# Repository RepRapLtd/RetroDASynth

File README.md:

# RetroDASynth

**RetroDASynth** is an open-source project to build a modular, polyphonic, retro-style electronic music synthesiser from inexpensive, readily available components. Its central idea is to use **the same general-purpose circuit board for different synthesiser modules**: load different software onto its microcontroller, and the board can become a voltage-controlled oscillator (VCO), a voltage-controlled filter (VCF), an envelope generator, or potentially another audio or control function. Modules can then be connected to make different instruments and signal-processing arrangements.

The design aims to be accessible to hobbyists: through-hole components where practicable, hand-solderable PCBs, 3D-printable mechanical parts, straightforward 5 V power, and published hardware and software. The ultimate aim is a self-contained, MIDI-controlled, polyphonic instrument, with sequencing and facilities for experimenting with the signal chain.

It is being created by Adrian Bowyer with significant inputs from ChatGPT.

## The prototype so far

The photograph above shows the current experimental system. **A working monophonic MIDI-controlled voice** has been demonstrated, using:

- An **Arduino UNO R4 WiFi** as the MIDI receiver and controller. It reads MIDI note messages, generates a pitch-control voltage and drives an active-low gate output.
- An **AVR32DA28** programmed as a VCO, producing audio using its internal DAC.
- A second **AVR32DA28** programmed as an envelope generator; its control voltage adjusts the VCO's output level.
- An **MCP6004** quad operational amplifier for analogue buffering and related signal conditioning.
- A **128 × 64 I²C OLED** on the Arduino, showing MIDI status, the last note, velocity and current monophonic voice activity.

The complete assembled prototype runs from a **single regulated 5 V supply**. In one test it drew approximately **109 mA** at 5 V (about 0.55 W), and played in tune. That measurement is for the present prototype, not a forecast for the finished polyphonic instrument.

## One board, several functions

The common module design is based on the **Microchip AVR32DA28**, a 28-pin, through-hole microcontroller with analogue-to-digital conversion, a digital-to-analogue converter, timers and digital I/O. The idea is to standardise the connections to controls, patch sockets and power, while changing the firmware to determine each module's behaviour.

The following functions have been developed and tested experimentally:

### Voltage-controlled oscillator (VCO)

- Produces **sine**, **triangle/sawtooth**, **square/pulse**, and **noise** waveforms.
- Waveform selection, pitch, shape and amplitude are voltage- or switch-controlled.
- Uses the AVR's **10-bit DAC**, driven by a timer-based waveform generator.
- Provides a low-frequency mode, allowing the same oscillator design to generate slowly varying control signals.
- Uses a pitch relationship of approximately **0.75 V per octave** in the present software; this is a project-specific convention, **not** the more usual 1 V/octave analogue-synthesiser standard.
- The analogue circuit provides buffered and inverted outputs. A filtered PWM signal establishes the reference needed for the complementary output.

### Voltage-controlled filter (VCF)

- A software-defined, two-pole **state-variable filter**, developed and tested on the AVR32DA28.
- Switch-selectable **low-pass, high-pass, band-pass and notch** responses.
- Voltage-controlled cutoff and resonance, with an option to experiment with self-oscillation.
- Processes an analogue audio input through the microcontroller's ADC and DAC.

This filter has been tested as a separate module; it is **not yet part of the MIDI-controlled voice shown in the prototype photograph**. Input bias handling and gain/headroom are subjects for further development.

### Envelope generator

- Produces a control voltage in response to a gate signal.
- Adjustable attack, decay and level, with several selectable envelope shapes.
- Supports experiments with gated and one-shot behaviour.
- In the present prototype, the envelope controls the VCO's output amplitude.

## MIDI controller and display

The Arduino UNO R4 WiFi currently receives **DIN MIDI** via a MIDI shield and operates in a simple **monophonic** mode. Its DAC output on **A0** supplies pitch CV; digital pin **D2** supplies the active-low envelope gate. The small OLED is connected over I²C.

The current display shows the last MIDI note, its velocity, whether the single voice is active, and basic MIDI status. Features such as channel selection, polyphonic voice allocation, sustain-pedal handling and sequencing are **planned, not yet implemented**.

The prototype currently uses the R4's built-in DAC for pitch. For the polyphonic design, the intention is to use **a separate dual-channel, 12-bit SPI DAC for each voice** (a possible device is the through-hole **MCP4822**), providing independent **pitch and velocity/control voltages**. This is a design proposal, not an installed part of the photographed prototype.

## Intended polyphonic architecture

The proposed arrangement is:

1. The central Arduino receives MIDI and, eventually, runs a sequencer and allocates notes to available voices.
2. Each voice has its own pitch and amplitude-control voltages, plus an envelope gate.
3. Each voice is assembled from common programmable modules, initially an oscillator and envelope generator, with filters added as desired.
4. The audio outputs are mixed to produce the instrument's final sound.

A first polyphonic build will probably have a modest number of voices, with the design able to expand. Voice stealing, MIDI sustain and channel-specific controls will be addressed as the instrument develops.

## Hardware and software

The repository is organised into:

- [`Electronics/`](Electronics/) — electronic design material.
- [`Software/`](Software/) — firmware and related software.
- [`Docs/`](Docs/) — documentation.
- [`Pix/`](Pix/) — photographs and illustrations, including the prototype picture above.

Firmware development uses the **Arduino IDE** and **DxCore** for the AVR DA-series microcontrollers. The MIDI controller uses the Arduino UNO R4 WiFi environment. The electronic design work uses **KiCad**.

**Project status:** experimental development. The circuits and programs are evolving, and a tested breadboard prototype should not be mistaken for a final, documented, ready-to-build kit.

## Next steps

- Develop and manufacture the standard through-hole module PCB.
- Extend the controller from one note to multiple independently allocated voices.
- Move pitch and velocity/control outputs to external, per-voice SPI DACs.
- Add MIDI channel selection, diagnostics and sustain-pedal support.
- Integrate the filter into complete voices, and develop audio mixing.
- Add sequencing, and develop the interlocking 3D-printed module/panel system.

## Licence

This repository includes the [GNU General Public License, version 3](LICENSE). See that file for the applicable licence terms.

## Written by

Adrian Bowyer and ChatGPT

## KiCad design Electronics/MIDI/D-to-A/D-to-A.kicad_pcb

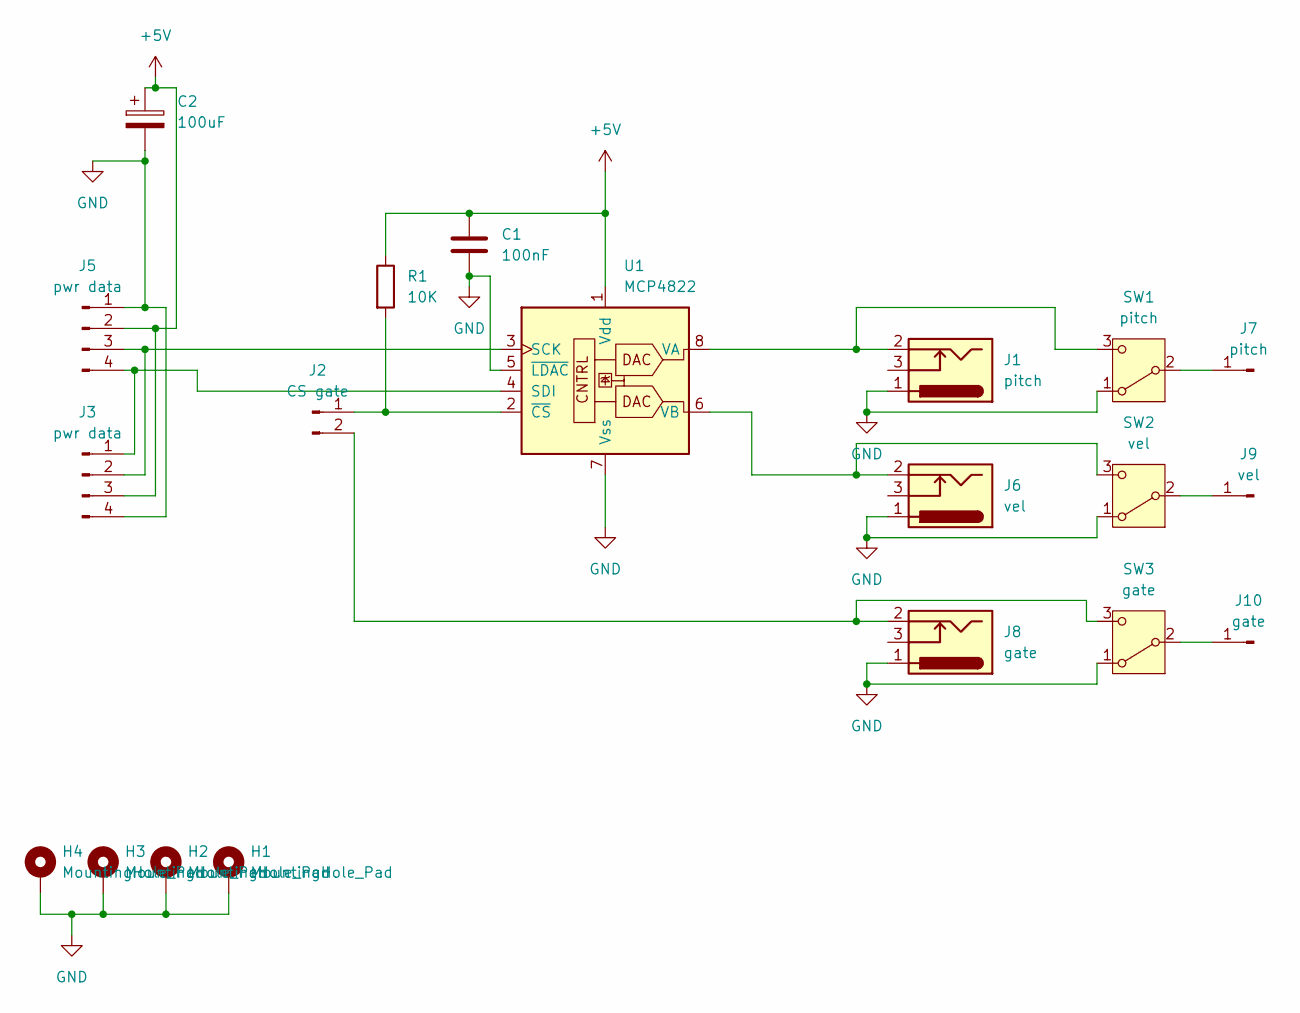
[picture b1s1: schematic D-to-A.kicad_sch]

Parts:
C1: 100nF; C_Disc_D3.4mm_W2.1mm_P2.50mm
C2: 100uF; CP_Radial_D6.3mm_P2.50mm
H1, H2, H3, H4: MountingHole_Pad; MountingHole_3.2mm_M3_DIN965_Pad
J1: pitch; barrel_jack_switch
J2: CS gate; PinHeader_1x02_P2.54mm_Horizontal
J3, J5: pwr data; PinHeader_1x04_P2.54mm_Horizontal
J6: vel; barrel_jack_switch
J7: pitch; PinHeader_1x01_P2.54mm_Horizontal
J8: gate; barrel_jack_switch
J9: vel; PinHeader_1x01_P2.54mm_Horizontal
J10: gate; PinHeader_1x01_P2.54mm_Horizontal
R1: 10K; R_Axial_DIN0204_L3.6mm_D1.6mm_P5.08mm_Horizontal
SW1: pitch; SW_1P2W
SW2: vel; SW_1P2W
SW3: gate; SW_1P2W
U1: MCP4822; DIP-8_W7.62mm

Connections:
+5V: C1.1, C2.1, J3.3, J5.2, R1.1, U1.1 (Vdd)
GND: C1.2, C2.2, H1.1 (1_1), H2.1 (1_1), H3.1 (1_1), H4.1 (1_1), J1.1, J3.4, J5.1, J6.1, J8.1, SW1.1 (A), SW2.1 (A), SW3.1 (A), U1.5 (~LDAC), U1.7 (Vss)
unnamed: J2.1, R1.2, U1.2 (~CS)
unnamed: J2.2, J8.2, SW3.3 (C)
unnamed: J3.1, J5.4, U1.4 (SDI)
unnamed: J3.2, J5.3, U1.3 (SCK)
unnamed: J7.1 (Pin_1_1), SW1.2 (B)
unnamed: J9.1 (Pin_1_1), SW2.2 (B)
unnamed: J10.1 (Pin_1_1), SW3.2 (B)
unnamed: J1.2, SW1.3 (C), U1.8 (VA)
unnamed: J6.2, SW2.3 (C), U1.6 (VB)

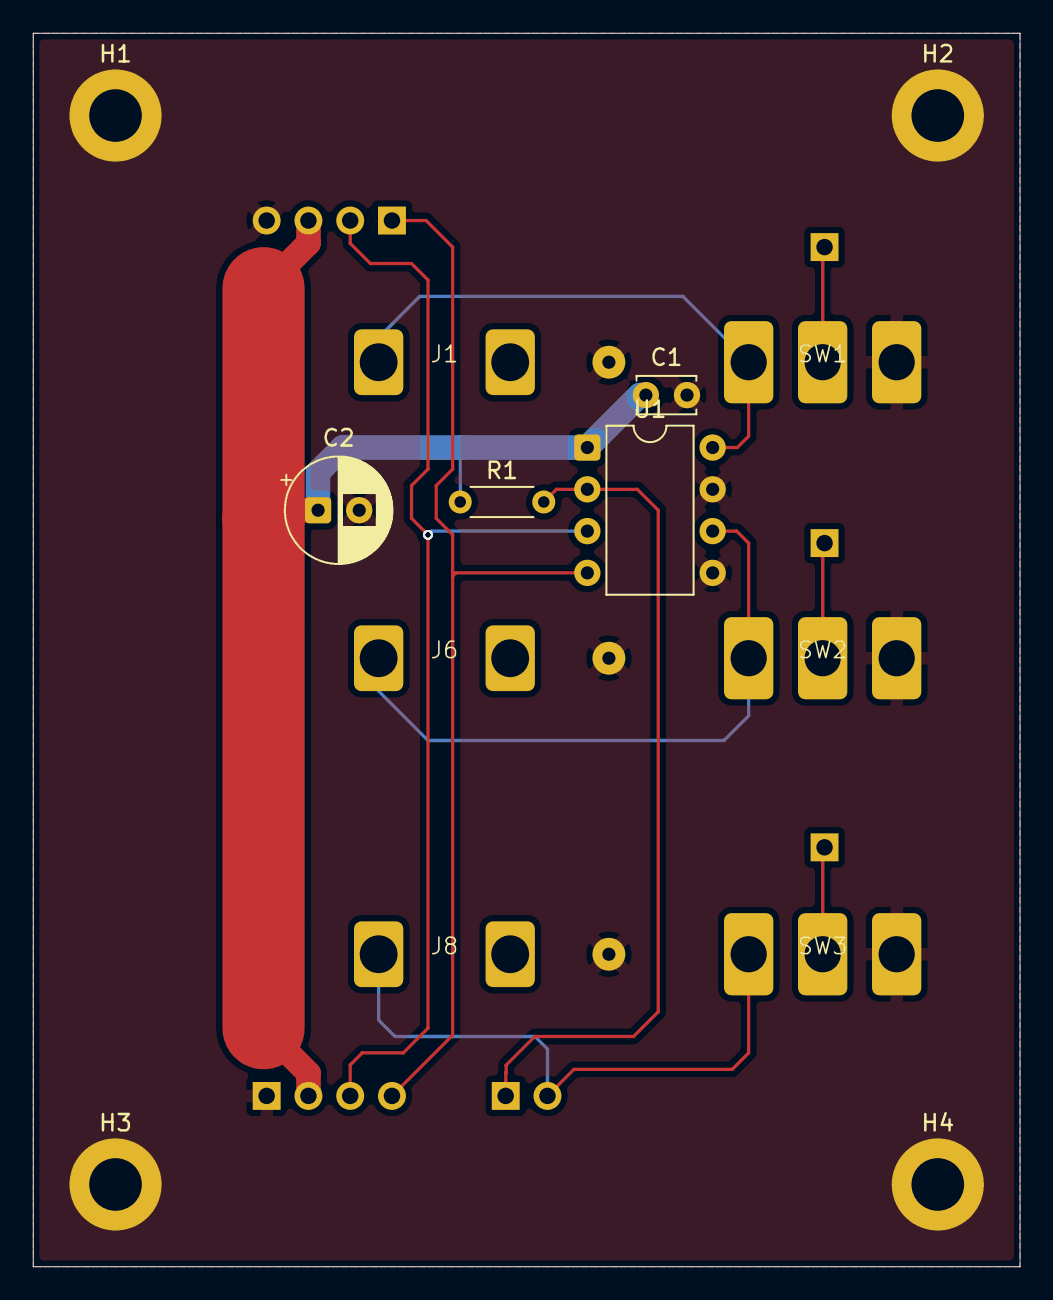
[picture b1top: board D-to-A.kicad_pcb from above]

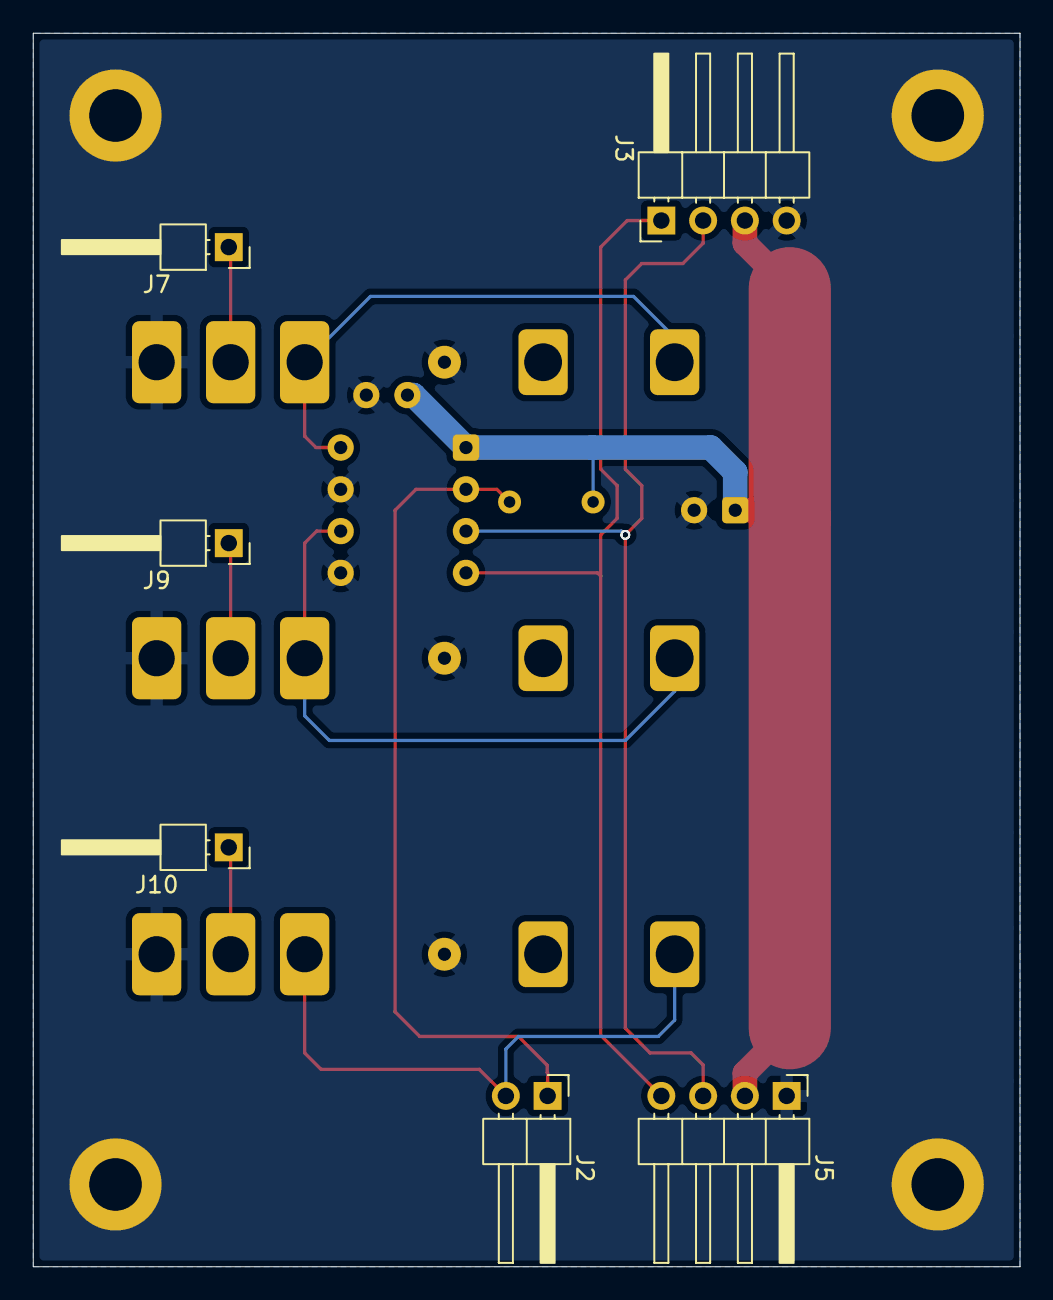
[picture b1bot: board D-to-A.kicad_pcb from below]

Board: 2 copper layers, 60.0 x 75.0 mm, 20 parts (6 on the bottom side), 11 nets.

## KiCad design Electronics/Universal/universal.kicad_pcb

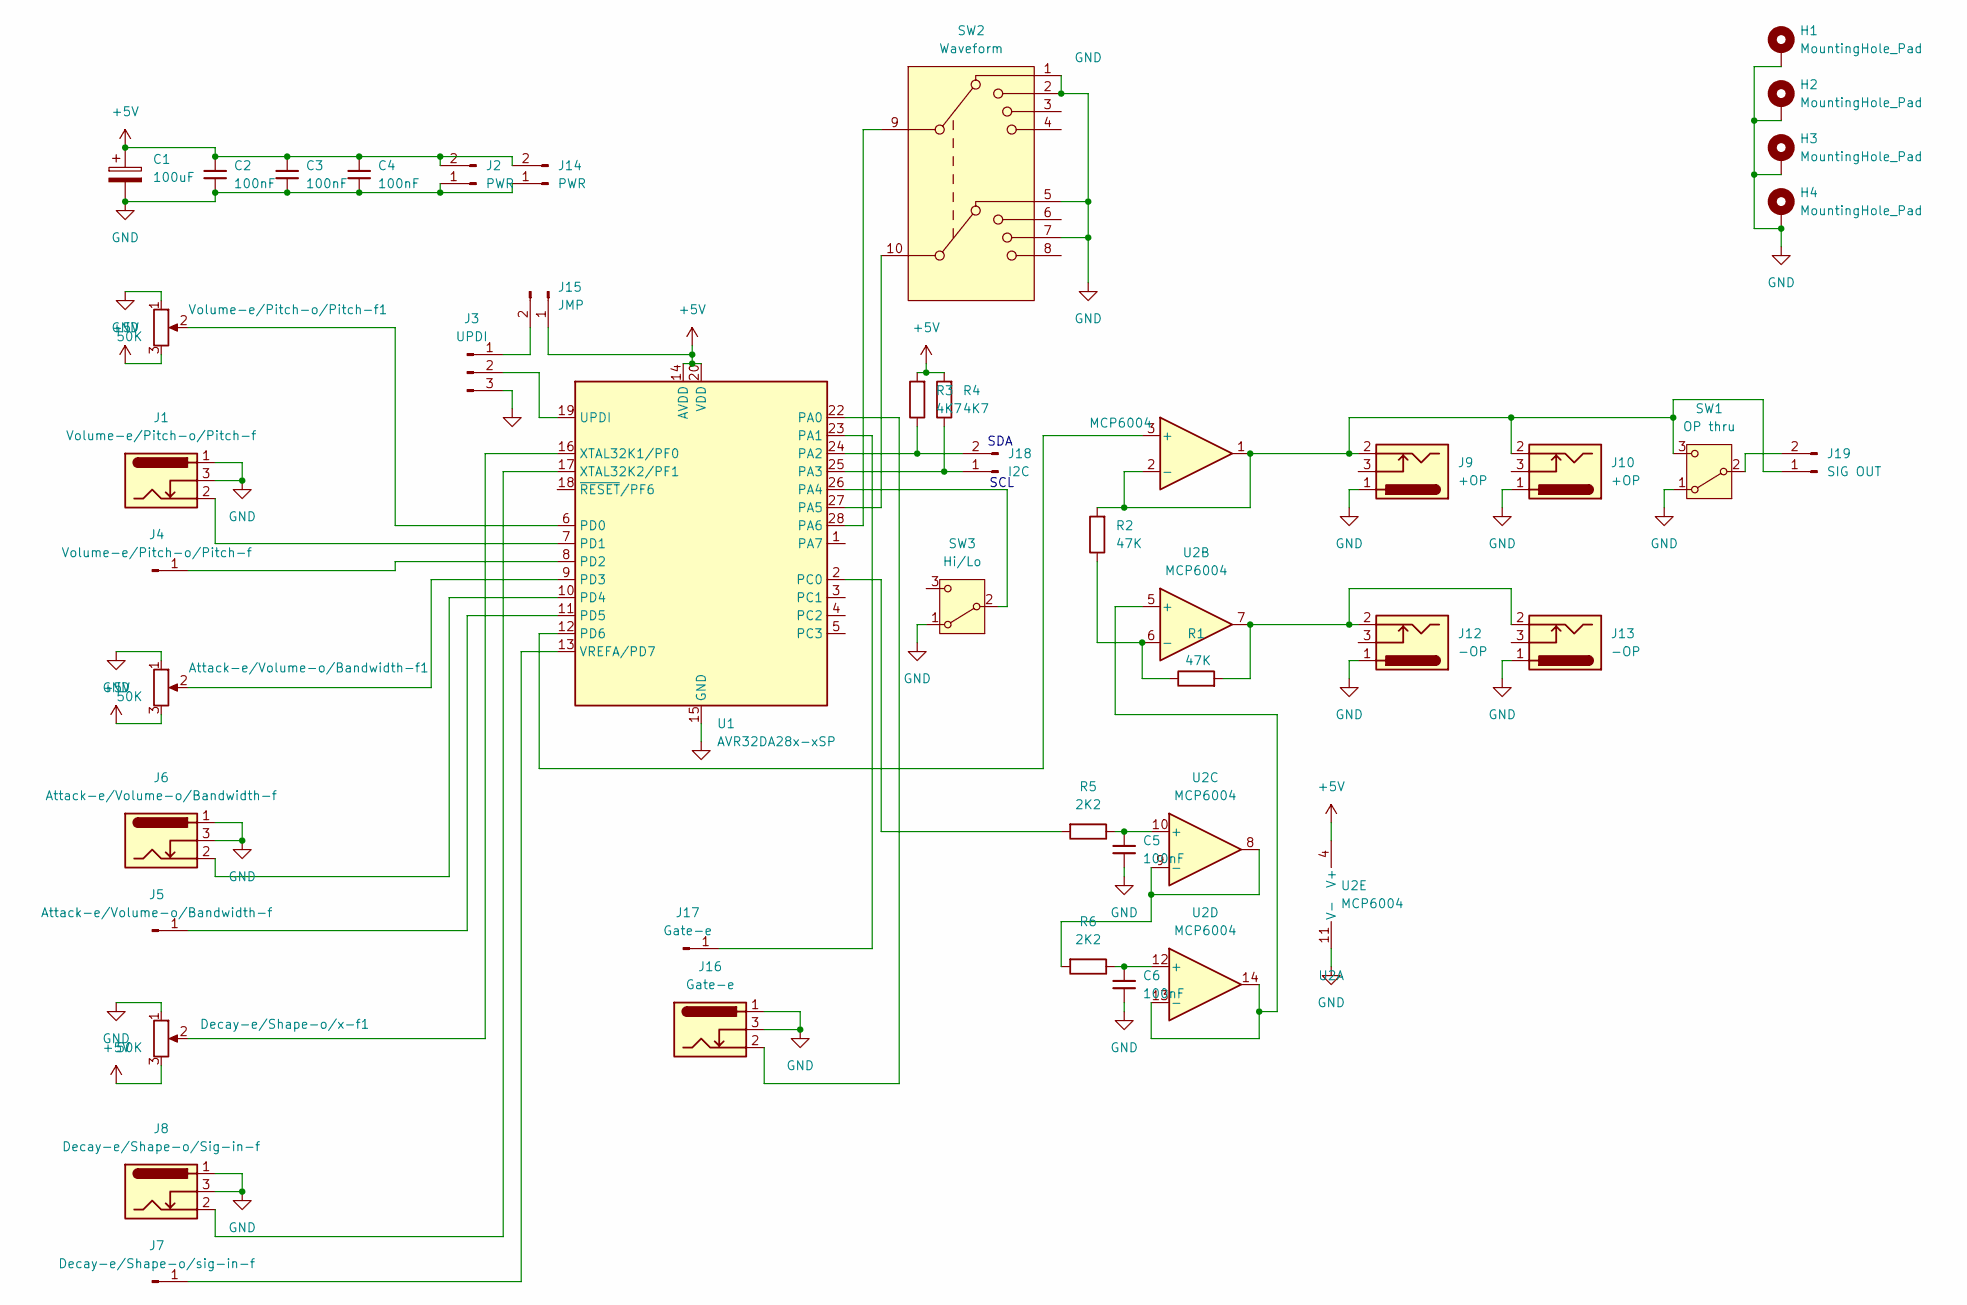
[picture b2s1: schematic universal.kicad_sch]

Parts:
Attack-e/Volume-o/Bandwidth-f1: 50K; Potentiometer_Alpha_RD901F-40-00D_Single_Vertical
C1: 100uF; C_Radial_D6.3mm_H11.0mm_P2.50mm
C2, C3, C4, C5, C6: 100nF; C_Disc_D3.0mm_W1.6mm_P2.50mm
Decay-e/Shape-o/x-f1: 50K; Potentiometer_Alpha_RD901F-40-00D_Single_Vertical
H1, H2, H3, H4: MountingHole_Pad; MountingHole_3.2mm_M3_Pad
J1: Volume-e/Pitch-o/Pitch-f; barrel_jack_switch
J2, J14: PWR; PinHeader_1x02_P2.54mm_Horizontal
J3: UPDI; PinSocket_1x03_P2.54mm_Vertical
J4: Volume-e/Pitch-o/Pitch-f; PinHeader_1x01_P2.54mm_Horizontal
J5: Attack-e/Volume-o/Bandwidth-f; PinHeader_1x01_P2.54mm_Horizontal
J6: Attack-e/Volume-o/Bandwidth-f; barrel_jack_switch
J7: Decay-e/Shape-o/sig-in-f; PinHeader_1x01_P2.54mm_Horizontal
J8: Decay-e/Shape-o/Sig-in-f; barrel_jack_switch
J9, J10: +OP; barrel_jack_switch
J12, J13: -OP; barrel_jack_switch
J15: JMP; PinHeader_1x02_P2.54mm_Vertical
J16: Gate-e; barrel_jack_switch
J17: Gate-e; PinHeader_1x01_P2.54mm_Horizontal
J18: I2C; PinHeader_1x02_P2.54mm_Vertical
J19: SIG OUT; PinHeader_1x02_P2.54mm_Horizontal
R1, R2: 47K; R_Axial_DIN0204_L3.6mm_D1.6mm_P5.08mm_Horizontal
R3, R4: 4K7; R_Axial_DIN0204_L3.6mm_D1.6mm_P5.08mm_Horizontal
R5, R6: 2K2; R_Axial_DIN0204_L3.6mm_D1.6mm_P5.08mm_Horizontal
SW1: OP thru; SW_1P2W
SW2: Waveform; rotary_2p4w
SW3: Hi/Lo; SW_1P2W
U1: AVR32DA28x-xSP; DIP-28_W7.62mm
U2: MCP6004; DIP-14_W7.62mm
Volume-e/Pitch-o/Pitch-f1: 50K; Potentiometer_Alpha_RD901F-40-00D_Single_Vertical

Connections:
+5V: Attack-e/Volume-o/Bandwidth-f1.3, C1.1, C2.1, C3.1, C4.1, Decay-e/Shape-o/x-f1.3, J2.2, J14.2, J15.1, R3.2, R4.2, U1.14 (AVDD), U1.20 (VDD), U2.4 (V+), Volume-e/Pitch-o/Pitch-f1.3
GND: Attack-e/Volume-o/Bandwidth-f1.1, C1.2, C2.2, C3.2, C4.2, C5.2, C6.2, Decay-e/Shape-o/x-f1.1, H1.1 (1_1), H2.1 (1_1), H3.1 (1_1), H4.1 (1_1), J1.1, J1.3, J2.1, J3.3, J6.1, J6.3, J8.1, J8.3, J9.1, J10.1, J12.1, J13.1, J14.1, J16.1, J16.3, SW1.1 (A), SW2.1, SW2.2, SW2.5, SW2.7, SW3.1 (A), U1.15 (GND), U1.21 (GND), U2.11 (V-), Volume-e/Pitch-o/Pitch-f1.1
unnamed: J3.2, U1.19 (UPDI)
unnamed: J4.1 (Pin_1_1), U1.8 (PD2)
unnamed: J5.1 (Pin_1_1), U1.11 (PD5)
unnamed: J7.1 (Pin_1_1), U1.13 (VREFA/PD7)
unnamed: J12.2, J13.2, R1.2, U2.7
unnamed: J3.1, J15.2
unnamed: J17.1 (Pin_1_1), U1.23 (PA1)
unnamed: J18.1, R4.1, U1.25 (PA3)
unnamed: J18.2, R3.1, U1.24 (PA2)
unnamed: J9.2, J10.2, J19.1, R2.2, SW1.3 (C), U2.1, U2.2 (-)
unnamed: J19.2, SW1.2 (B)
unnamed: SW3.2 (B), U1.26 (PA4)
unnamed: J16.2, U1.22 (PA0)
unnamed: SW2.10, U1.27 (PA5)
unnamed: SW2.9, U1.28 (PA6)
unnamed: R5.2, U1.2 (PC0)
unnamed: U1.6 (PD0), Volume-e/Pitch-o/Pitch-f1.2
unnamed: J1.2, U1.7 (PD1)
unnamed: Attack-e/Volume-o/Bandwidth-f1.2, U1.9 (PD3)
unnamed: J6.2, U1.10 (PD4)
unnamed: U1.12 (PD6), U2.3 (+)
unnamed: Decay-e/Shape-o/x-f1.2, U1.16 (XTAL32K1/PF0)
unnamed: J8.2, U1.17 (XTAL32K2/PF1)
unnamed: U2.5 (+), U2.13 (-), U2.14
unnamed: R1.1, R2.1, U2.6 (-)
unnamed: C5.1, R5.1, U2.10 (+)
unnamed: R6.2, U2.8, U2.9 (-)
unnamed: C6.1, R6.1, U2.12 (+)

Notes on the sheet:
SCL
SDA

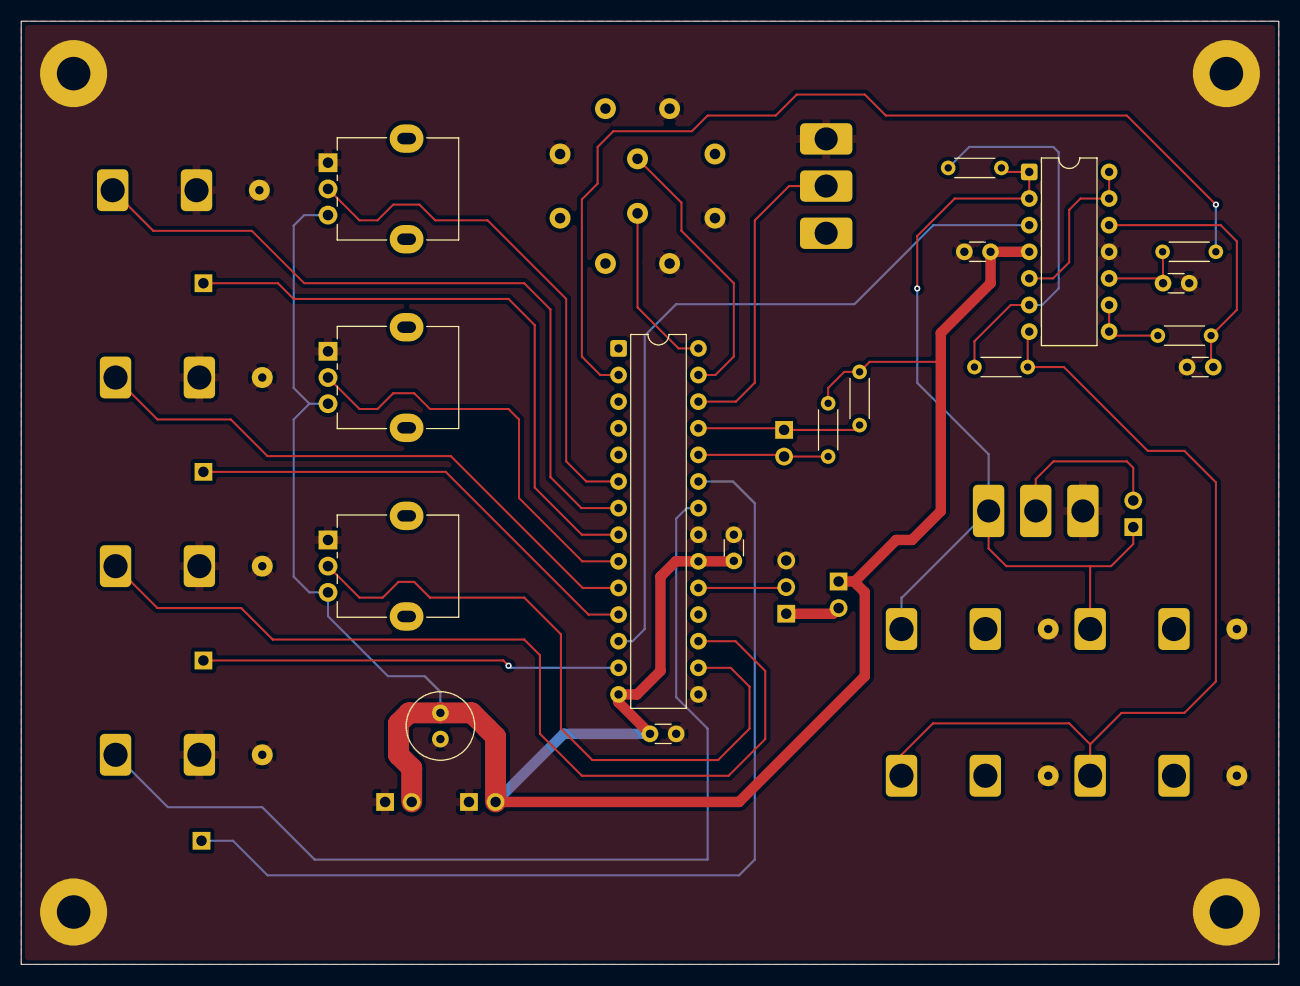
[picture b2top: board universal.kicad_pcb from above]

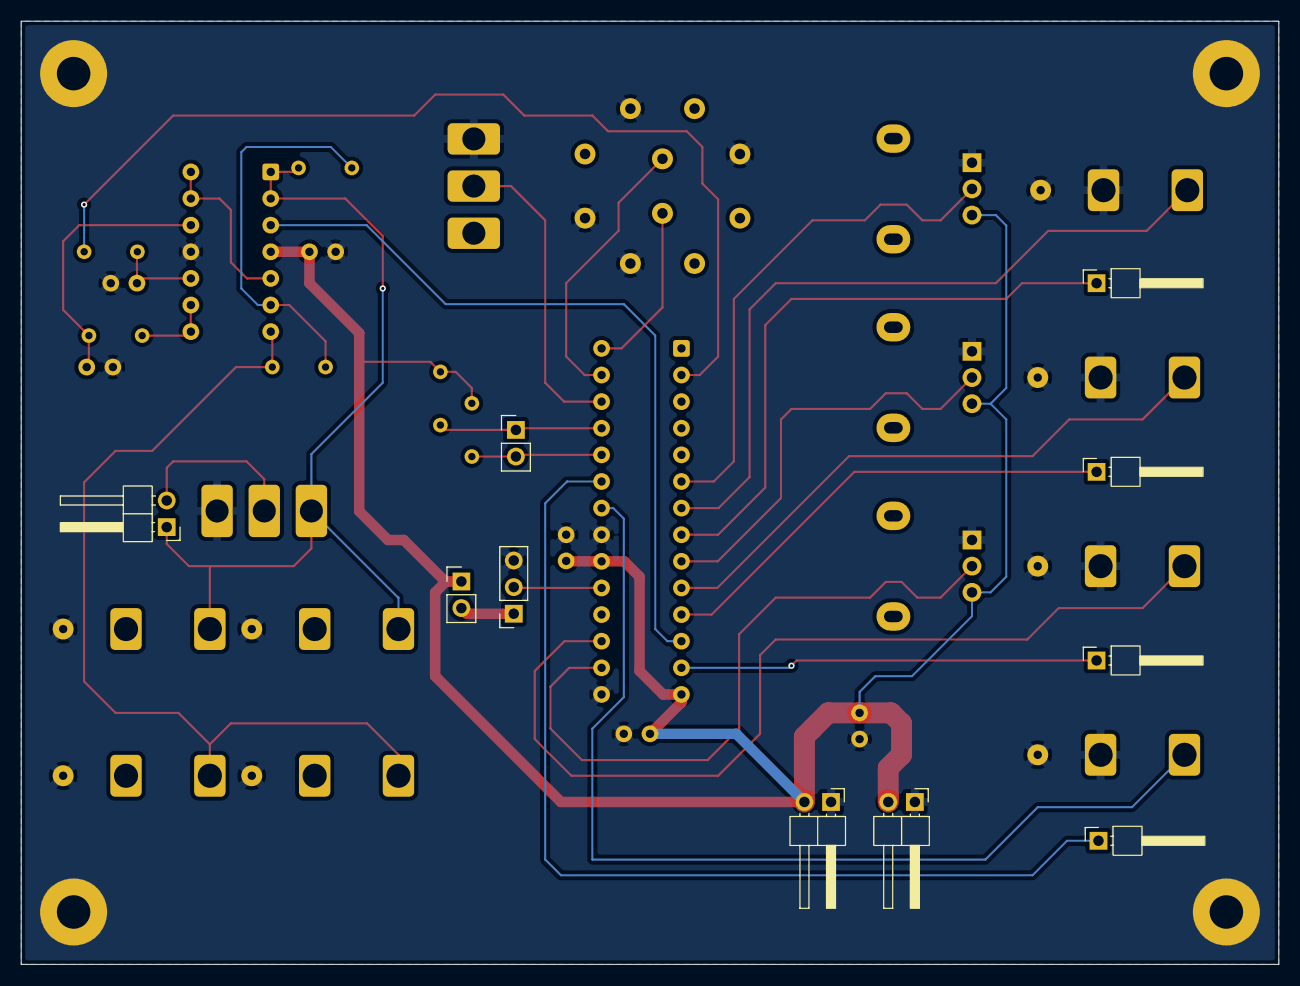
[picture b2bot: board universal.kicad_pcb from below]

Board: 2 copper layers, 120.0 x 90.0 mm, 42 parts (10 on the bottom side), 30 nets.

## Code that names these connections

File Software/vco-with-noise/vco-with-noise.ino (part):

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//
// DxCore 1.6.2, 24 MHz internal clock
//
// PD0  Pitch CV
// PD1  Pitch CV
// PD2  Pitch CV
// PD3  Volume CV
// PD4  Volume CV
// PD5  Volume CV
// PD7  Shape CV
// PF0  Shape CV
// PF1  Shape CV
// PD6  10-bit DAC output
//
// PC0  PWM reference output (93.75 kHz)
//
// PA4  Frequency range (LOW = low range)
// PA5  Waveform bit 0
// PA6  Waveform bit 1
//
// Waveforms:
//   3 Sine
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// TCA0, single-slope PWM
// 24 MHz / 256 = 93750 Hz
//
// WO0 routed to PC0.
// ============================================================

void setupPWM()
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  PORTMUX.TCAROUTEA =
      PORTMUX_TCA0_PORTC_gc;

  pinMode(PIN_PC0, OUTPUT);

  TCA0.SINGLE.CTRLA = 0;

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
void setup()
{
  pinMode(PIN_PA4, INPUT_PULLUP);
  pinMode(PIN_PA5, INPUT_PULLUP);
  pinMode(PIN_PA6, INPUT_PULLUP);

  pinMode(PIN_PD0, INPUT);
  pinMode(PIN_PD1, INPUT);
  pinMode(PIN_PD2, INPUT);
  pinMode(PIN_PD3, INPUT);
  pinMode(PIN_PD4, INPUT);
  pinMode(PIN_PD5, INPUT);
  pinMode(PIN_PD7, INPUT);
  pinMode(PIN_PF0, INPUT);
  pinMode(PIN_PF1, INPUT);
    
  analogReadResolution(12);
  analogReference(VDD);
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      (VREF.ADC0REF & ~VREF_REFSEL_gm) |
      VREF_REFSEL_VDD_gc;

  (void)analogRead(PIN_PD0);
  (void)analogRead(PIN_PD1);
  (void)analogRead(PIN_PD2);
  (void)analogRead(PIN_PD3);
  (void)analogRead(PIN_PD4);
  (void)analogRead(PIN_PD5);
  (void)analogRead(PIN_PD7);
  (void)analogRead(PIN_PF0);
  (void)analogRead(PIN_PF1);

  // Enable DAC
  DACReference(VDD);
  analogWrite(PIN_PD6, 128);
  DAC0.DATA = 0;

  // PWM reference output
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
  // ---- Read analogue controls ----

  uint16_t pitchADC = analogRead(PIN_PD0)
                  + analogRead(PIN_PD1)
                  + analogRead(PIN_PD2);

  uint16_t volumeADC =
      analogRead(PIN_PD3)
      + analogRead(PIN_PD4)
      + analogRead(PIN_PD5);
      
  uint16_t shapeADC = analogRead(PIN_PD7)
      + analogRead(PIN_PF0)
      + analogRead(PIN_PF1);

  // ---- Waveform selection ----

  uint8_t selected =
      (!digitalRead(PIN_PA5) ? 0 : 1) |
      (!digitalRead(PIN_PA6) ? 0 : 2);

  uint8_t shape = shapeADC >> 4;

  bool lowRange = !digitalRead(PIN_PA4);
  bool drifting = (selected == 3 && lowRange);

  if (selected != oldWaveform ||
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
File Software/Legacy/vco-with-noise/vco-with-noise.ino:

#include <Arduino.h>
#include <math.h>

// -------- User settings --------

const uint8_t DAC_P   = PIN_PA6;
const uint8_t CV_P    = PIN_PA2;
const uint8_t WAVE_P  = PIN_PA1;
const uint8_t SHAPE_P = PIN_PA3;
const uint8_t AMP_P   = PIN_PA7;  // NEW

const uint32_t SAMPLE_RATE = 40000;

const float MIN_FREQ = 50.0f;
const float VOLTS_PER_OCTAVE = 0.75f;
const float SUPPLY_VOLTAGE = 5.0f;

const uint8_t LOW_LEVEL  = 8;
const uint8_t HIGH_LEVEL = 248;
const uint8_t MID_LEVEL  = 128;

// Waveform numbers
const uint8_t SINE     = 0;
const uint8_t TRIANGLE = 1;
const uint8_t SQUARE   = 2;
const uint8_t NOISE    = 3;

// -------- Quarter-sine table in flash --------

const uint8_t sineTable[65] = {
  128,131,134,137,140,143,146,149,
  151,154,157,160,163,166,168,171,
  174,177,179,182,185,187,190,192,
  195,197,199,202,204,206,209,211,
  213,215,217,219,221,223,224,226,
  228,229,231,232,234,235,236,238,
  239,240,241,242,243,244,244,245,
  246,246,247,247,247,248,248,248,
  248
};

// -------- Oscillator state --------

volatile uint32_t phase = 0;
volatile uint32_t phaseIncrement = 0;

volatile uint8_t waveform = SINE;

volatile uint16_t trianglePeak = 128;
volatile uint16_t riseScale = 480;
volatile uint16_t fallScale = 480;

volatile uint8_t pulseWidth = 128;

// NEW: amplitude, 0 to 255
volatile uint8_t amplitude = 0;

// 32-bit white noise generator
uint32_t rng = 0xACE12345;

// -------- Waveform interrupt --------


ISR(TCB0_INT_vect)
{
  phase += phaseIncrement;

  uint8_t p = phase >> 24;
  uint8_t output;

  // -------- Generate waveform --------

  if (waveform == SINE)
  {
    uint8_t q = p >> 6;
    uint8_t i = p & 63;

    switch (q)
    {
      case 0:
        output = sineTable[i];
        break;

      case 1:
        output = sineTable[64 - i];
        break;

      case 2:
        output = 256 - sineTable[i];
        break;

      default:
        output = 256 - sineTable[64 - i];
        break;
    }
  }
  else if (waveform == TRIANGLE)
  {
    if (p < trianglePeak)
    {
      output = LOW_LEVEL +
        (((uint32_t)p * riseScale) >> 8);
    }
    else
    {
      output = LOW_LEVEL +
        (((uint32_t)(256 - p) * fallScale) >> 8);
    }
  }
  else if (waveform == SQUARE)
  {
    output = (p < pulseWidth) ?
      HIGH_LEVEL : LOW_LEVEL;
  }
  else
  {
    // White noise: 32-bit xorshift
    rng ^= rng << 13;
    rng ^= rng >> 17;
    rng ^= rng << 5;

    output = LOW_LEVEL +
      (((uint16_t)(uint8_t)rng * 240) >> 8);
  }

  // -------- Smooth amplitude --------

  // 16 fractional bits for precision
  static int32_t smoothAmp = 0;

  // Convert requested amplitude to fixed point
  int32_t targetAmp = (int32_t)amplitude << 16;

  // First-order low-pass filter
  // Time constant approximately 25.6 ms
  smoothAmp += (targetAmp - smoothAmp) >> 10;

  // Recover 8-bit amplitude
  uint8_t currentAmp = smoothAmp >> 16;

  // -------- Apply amplitude --------

  // Centre waveform around zero
  int16_t centred = (int16_t)output - MID_LEVEL;

  // Multiply by smoothed amplitude
  int32_t scaled = (int32_t)centred * currentAmp;

  // Restore midpoint and output to DAC
  DAC0.DATA = MID_LEVEL + (scaled >> 8);

  // Clear timer interrupt flag
  TCB0.INTFLAGS = TCB_CAPT_bm;
}


// -------- Initialisation --------

void setup()
{
  DACReference(INTERNAL4V3);
  analogWrite(DAC_P, MID_LEVEL);

  analogReference(VDD);

  pinMode(CV_P, INPUT);
  pinMode(WAVE_P, INPUT);
  pinMode(SHAPE_P, INPUT);
  pinMode(AMP_P, INPUT);  // NEW

  // Configure 40 kHz timer
  TCB0.CTRLA = 0;
  TCB0.CTRLB = TCB_CNTMODE_INT_gc;

  TCB0.CCMP = (F_CPU / SAMPLE_RATE) - 1;

  TCB0.INTFLAGS = TCB_CAPT_bm;
  TCB0.INTCTRL = TCB_CAPT_bm;

  TCB0.CTRLA =
    TCB_CLKSEL_CLKDIV1_gc | TCB_ENABLE_bm;
}

// -------- Main control loop --------

void loop()
{
  static int32_t filteredADC = -1;
  static uint8_t waveCounter = 0;
  static uint8_t selectedWave = SINE;

  // ----- Exponential frequency control -----

  uint16_t adc = analogRead(CV_P);

  int32_t target = (int32_t)adc * 256;

  if (filteredADC < 0)
  {
    filteredADC = target;
  }
  else if (abs(target - filteredADC) > 2048)
  {
    filteredADC = target;
  }
  else
  {
    filteredADC += (target - filteredADC) / 16;
  }

  float voltage =
    (filteredADC / 256.0f) *
    SUPPLY_VOLTAGE / 1023.0f;

  float frequency =
    MIN_FREQ * powf(2.0f,
      voltage / VOLTS_PER_OCTAVE);

  uint32_t increment =
    (uint32_t)(frequency *
               4294967296.0 / SAMPLE_RATE);

  // ----- Four-position waveform selector -----

  if (++waveCounter >= 20)
  {
    waveCounter = 0;

    uint16_t w = analogRead(WAVE_P);

    if (w < 170)
      selectedWave = SINE;
    else if (w < 512)
      selectedWave = TRIANGLE;
    else if (w < 852)
      selectedWave = SQUARE;
    else
      selectedWave = NOISE;
  }

  // ----- Waveform shaping -----

  uint16_t shape = analogRead(SHAPE_P);

  uint16_t peak = 128 +
    ((uint32_t)shape * 128 / 1023);

  uint16_t rising =
    ((uint32_t)240 * 256) / peak;

  uint16_t falling = 0;

  if (peak < 256)
  {
    falling =
      ((uint32_t)240 * 256) / (256 - peak);
  }

  uint8_t width = 128 -
    ((uint32_t)shape * 96 / 1023);

  // ----- NEW: amplitude control -----

  uint16_t ampADC = analogRead(AMP_P);

  // Scale 10-bit ADC to 8-bit amplitude
  uint8_t newAmplitude = ampADC >> 2;

  // ----- Atomic state update -----

  noInterrupts();

  phaseIncrement = increment;
  waveform = selectedWave;
  trianglePeak = peak;
  riseScale = rising;
  fallScale = falling;
  pulseWidth = width;
  amplitude = newAmplitude;

  interrupts();

  delay(5);
}
